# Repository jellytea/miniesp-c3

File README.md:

# MiniESP-C3 KiCad Project
M.2 core board designed for ESP32-C3

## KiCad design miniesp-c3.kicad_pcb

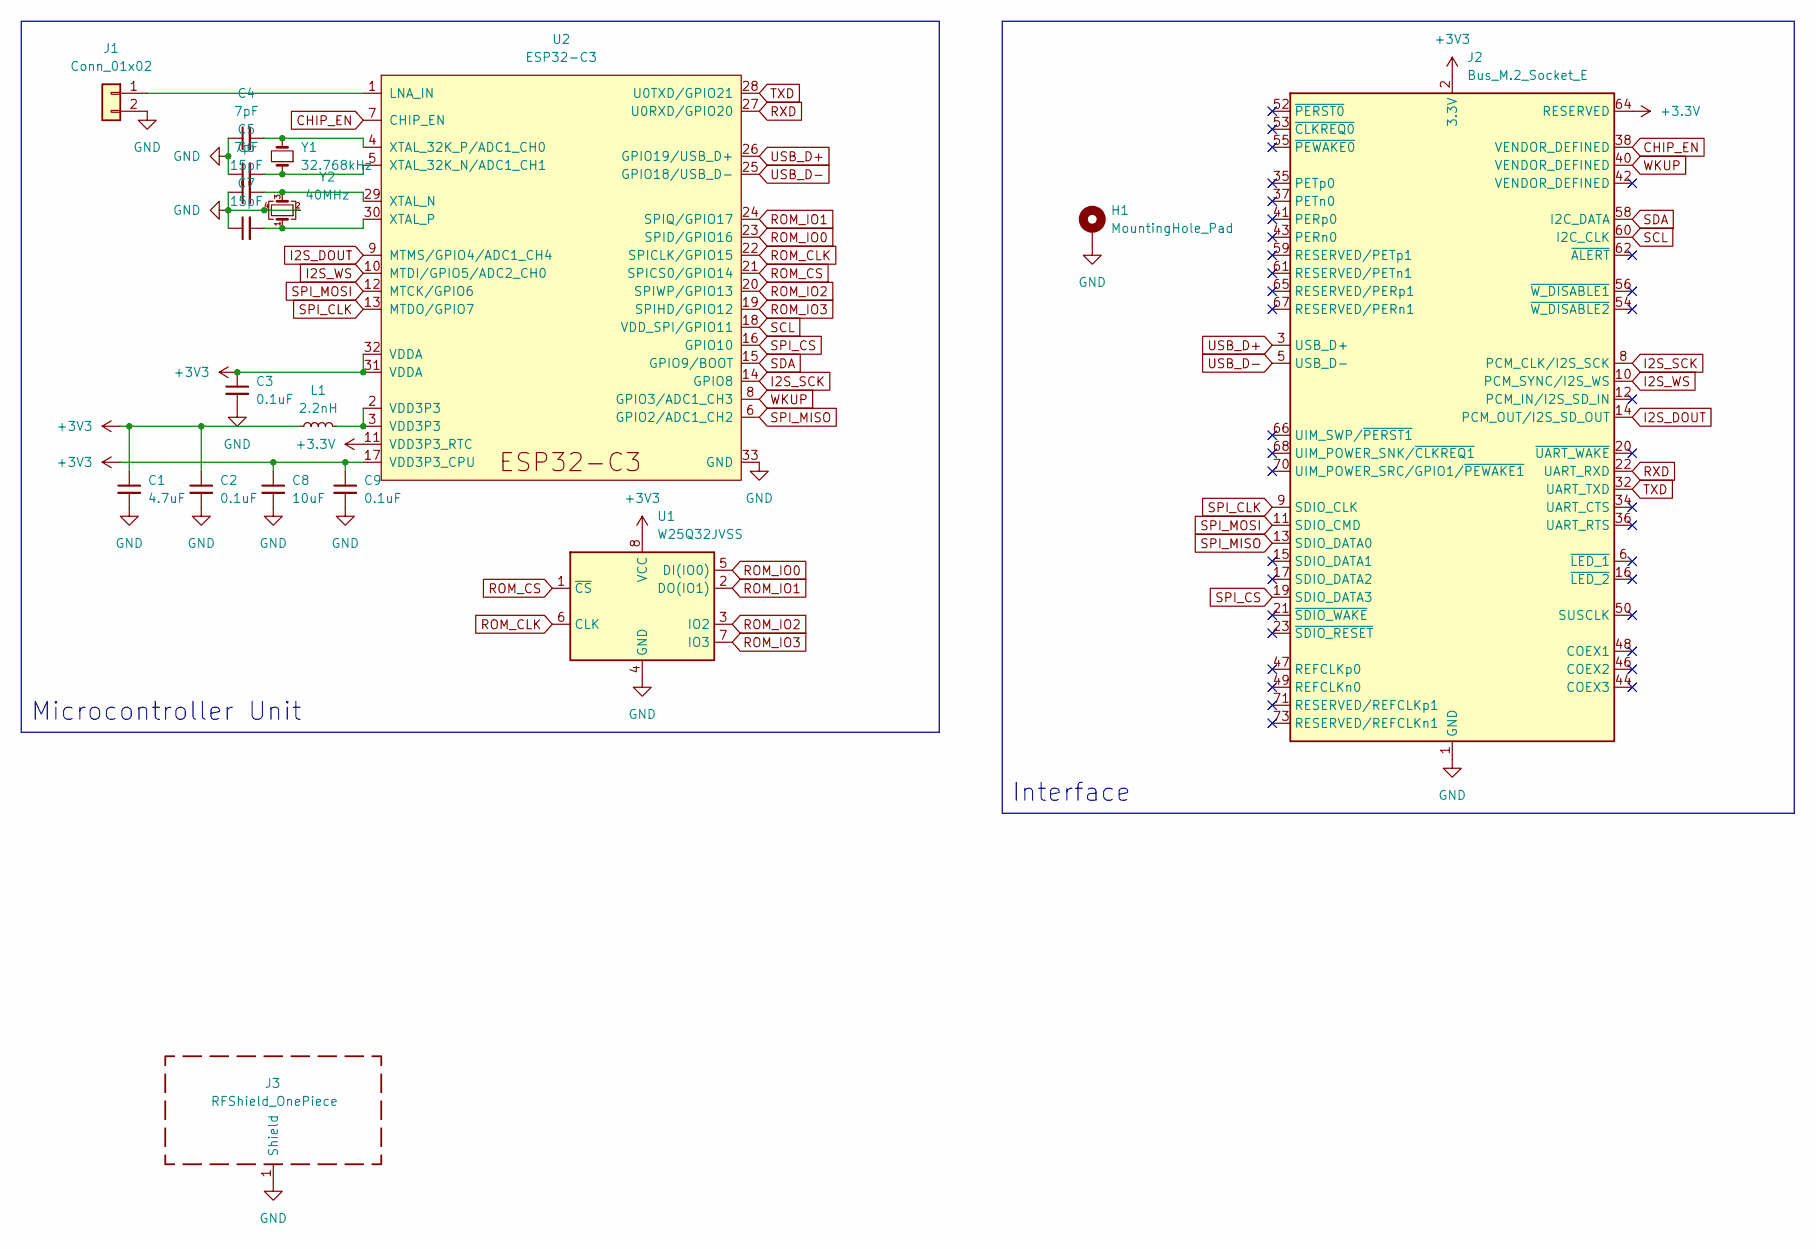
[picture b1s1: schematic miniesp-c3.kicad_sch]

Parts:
C1: 4.7uF; C_0603_1608Metric
C2, C3, C9: 0.1uF; C_0603_1608Metric
C4, C5: 7pF; C_0402_1005Metric
C6, C7: 15pF; C_0402_1005Metric
C8: 10uF; C_0603_1608Metric
H1: MountingHole_Pad; b5ac07d7-f8d1-48bd-96f9-ddd14d7acfe7
J1: Conn_01x02; U.FL_Hirose_U.FL-R-SMT-1_Vertical
J2: Bus_M.2_Socket_E; M.2_E
J3: RFShield_OnePiece; Wuerth_36103205_20x20mm
L1: 2.2nH; L_0603_1608Metric
U1: W25Q32JVSS; SOIC-8_5.23x5.23mm_P1.27mm
U2: ESP32-C3; QFN-32-1EP_5x5mm_P0.5mm_EP3.45x3.45mm_ThermalVias
Y1: 32.768kHz; Crystal_SMD_3215-2Pin_3.2x1.5mm
Y2: 40MHz; Crystal_SMD_3225-4Pin_3.2x2.5mm

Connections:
+3.3V: J2.64 (RESERVED), U2.11 (VDD3P3_RTC)
+3V3: C1.1, C2.1, C3.1, C8.1, C9.1, J2.2 (3.3V), J2.4 (3.3V), J2.72 (3.3V), J2.74 (3.3V), L1.1, U1.8 (VCC), U2.17 (VDD3P3_CPU), U2.31 (VDDA), U2.32 (VDDA)
CHIP_EN: J2.38 (VENDOR_DEFINED), U2.7 (CHIP_EN)
GND: C1.2, C2.2, C3.2, C4.1, C5.1, C6.1, C7.1, C8.2, C9.2, H1.1, J1.2, J2.1 (GND), J2.7 (GND), J2.18 (GND), J2.33 (GND), J2.39 (GND), J2.45 (GND), J2.51 (GND), J2.57 (GND), J2.63 (GND), J2.69 (GND), J2.75 (GND), J3.1 (Shield), U1.4 (GND), U2.33 (GND), Y2.2, Y2.4
I2S_DOUT: J2.14 (PCM_OUT/I2S_SD_OUT), U2.9 (MTMS/GPIO4/ADC1_CH4)
I2S_SCK: J2.8 (PCM_CLK/I2S_SCK), U2.14 (GPIO8)
I2S_WS: J2.10 (PCM_SYNC/I2S_WS), U2.10 (MTDI/GPIO5/ADC2_CH0)
unnamed: C4.2, U2.4 (XTAL_32K_P/ADC1_CH0), Y1.2
unnamed: C5.2, U2.5 (XTAL_32K_N/ADC1_CH1), Y1.1
unnamed: C6.2, U2.29 (XTAL_N), Y2.3
unnamed: C7.2, U2.30 (XTAL_P), Y2.1
unnamed: J1.1, U2.1 (LNA_IN)
unnamed: L1.2, U2.2 (VDD3P3), U2.3 (VDD3P3)
ROM_CLK: U1.6 (CLK), U2.22 (SPICLK/GPIO15)
ROM_CS: U1.1 (~CS), U2.21 (SPICS0/GPIO14)
ROM_IO0: U1.5 (DI(IO0)), U2.23 (SPID/GPIO16)
ROM_IO1: U1.2 (DO(IO1)), U2.24 (SPIQ/GPIO17)
ROM_IO2: U1.3 (IO2), U2.20 (SPIWP/GPIO13)
ROM_IO3: U1.7 (IO3), U2.19 (SPIHD/GPIO12)
RXD: J2.22 (UART_RXD), U2.27 (U0RXD/GPIO20)
SCL: J2.60 (I2C_CLK), U2.18 (VDD_SPI/GPIO11)
SDA: J2.58 (I2C_DATA), U2.15 (GPIO9/BOOT)
SPI_CLK: J2.9 (SDIO_CLK), U2.13 (MTDO/GPIO7)
SPI_CS: J2.19 (SDIO_DATA3), U2.16 (GPIO10)
SPI_MISO: J2.13 (SDIO_DATA0), U2.6 (GPIO2/ADC1_CH2)
SPI_MOSI: J2.11 (SDIO_CMD), U2.12 (MTCK/GPIO6)
TXD: J2.32 (UART_TXD), U2.28 (U0TXD/GPIO21)
USB_D+: J2.3 (USB_D+), U2.26 (GPIO19/USB_D+)
USB_D-: J2.5 (USB_D-), U2.25 (GPIO18/USB_D-)
WKUP: J2.40 (VENDOR_DEFINED), U2.8 (GPIO3/ADC1_CH3)

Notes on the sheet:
Interface
Microcontroller Unit

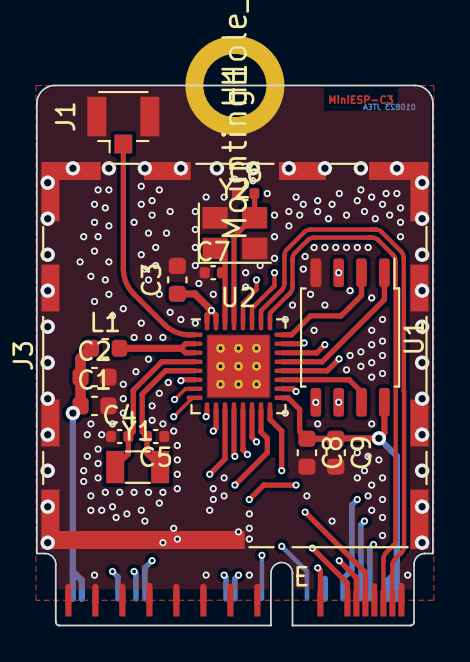
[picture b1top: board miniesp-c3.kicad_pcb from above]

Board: 4 copper layers, 22.0 x 30.0 mm, 18 parts (0 on the bottom side), 30 nets.

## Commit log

2023-01-10 Release.
